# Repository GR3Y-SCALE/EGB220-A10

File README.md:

# EGB220-A10 - Line follower robot

General repository for CAD models, PCB design and firmware.

## What is the directory structure?
The initial version of this github repository has several directories that contain relevant readmes similar to this one you are reading right now, they give an example of what goes into that directory.

## Questions?
Feel free to reach out to myself or other the other project members for details and clairifcation.

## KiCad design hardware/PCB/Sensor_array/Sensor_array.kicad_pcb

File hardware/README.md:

## This directory is for everything related to CAD, such as PCB design and BOMs and 3D models and acrylic cut out files for the line following robot.

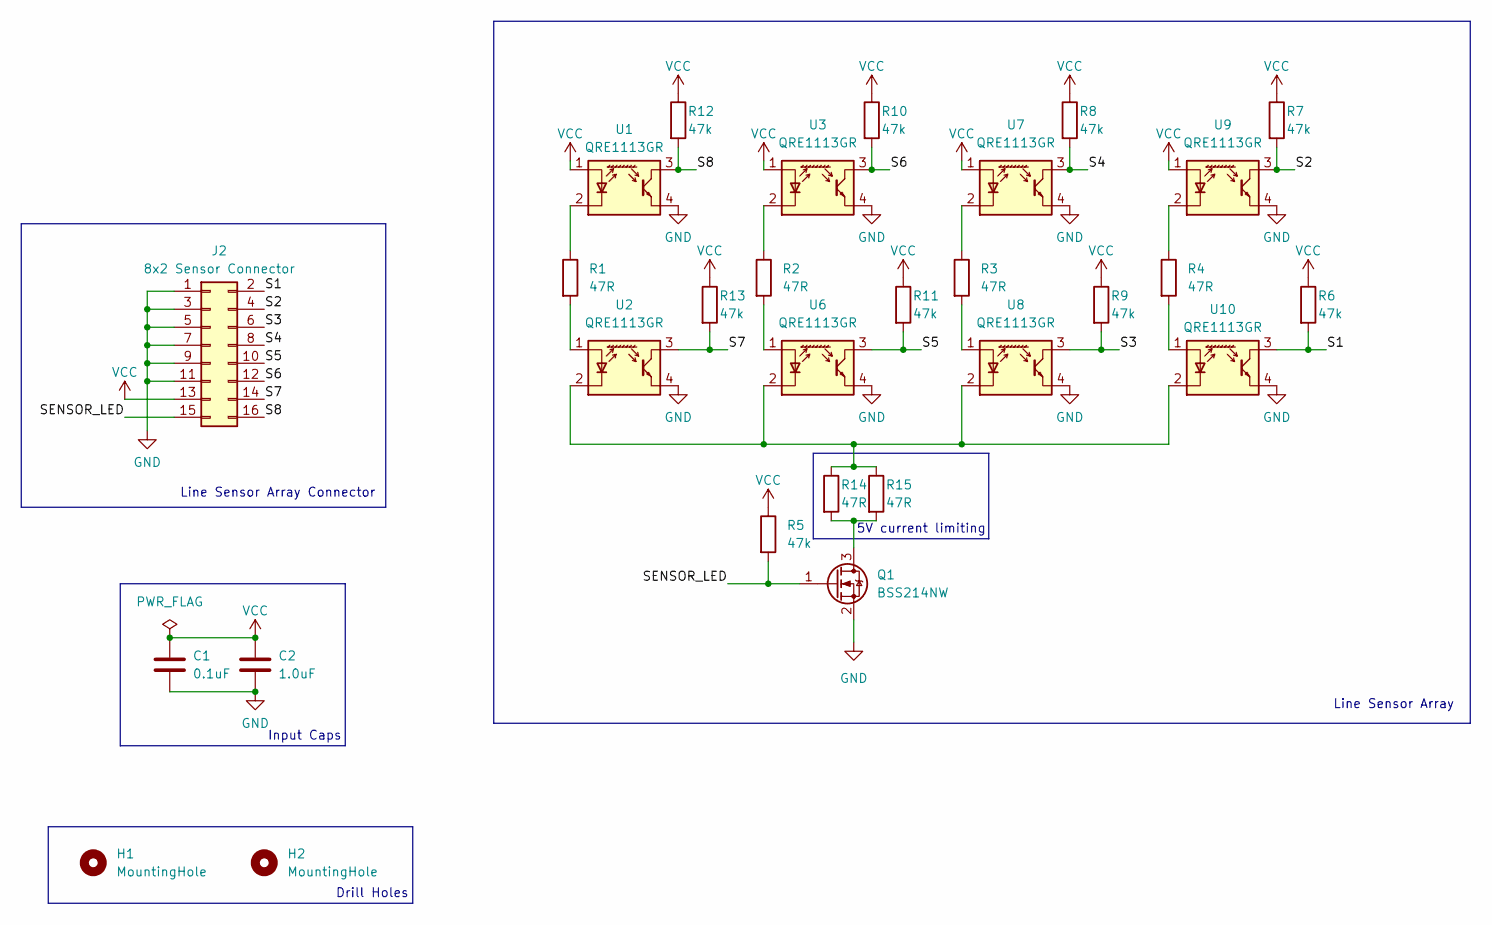
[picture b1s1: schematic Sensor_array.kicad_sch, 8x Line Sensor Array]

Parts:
C1: 0.1uF; C_0805_2012Metric; DigiKeyPartNumber 478-KGM21NR71H104KTTR-ND
C2: 1.0uF; C_0805_2012Metric; DigiKeyPartNumber 1276-1029-2-ND
H1, H2: MountingHole; MountingHole_2.2mm_M2
J2: 8x2 Sensor Connector; PinHeader_2x08_P2.54mm_Vertical
Q1: BSS214NW; SOT-323_SC-70; DigiKeyPartNumber QRE1113GRTR-ND
R1, R2, R3, R4, R14, R15: 47R; R_0805_2012Metric; DigiKeyPartNumber RMCF0805JT47R0TR-ND
R5, R6, R7, R8, R9, R10, R11, R12, R13: 47k; R_0805_2012Metric; DigiKeyPartNumber RMCF0805JT47K0TR-ND
U1, U2, U3, U6, U7, U8, U9, U10: QRE1113GR; OnSemi_CASE100CY

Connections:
/S1: J2.2, R6.2, U10.3
/S2: J2.4, R7.2, U9.3
/S3: J2.6, R9.2, U8.3
/S4: J2.8, R8.2, U7.3
/S5: J2.10, R11.2, U6.3
/S6: J2.12, R10.2, U3.3
/S7: J2.14, R13.2, U2.3
/S8: J2.16, R12.2, U1.3
/SENSOR_LED: J2.15, Q1.1 (G), R5.2
GND: C1.1, C2.1, J2.1, J2.3, J2.5, J2.7, J2.9, J2.11, Q1.2 (S), U1.4, U2.4, U3.4, U6.4, U7.4, U8.4, U9.4, U10.4
unnamed: Q1.3 (D), R14.2, R15.2
unnamed: R1.1, U1.2 (K)
unnamed: R1.2, U2.1 (A)
unnamed: R2.1, U3.2 (K)
unnamed: R2.2, U6.1 (A)
unnamed: R3.1, U7.2 (K)
unnamed: R3.2, U8.1 (A)
unnamed: R4.1, U9.2 (K)
unnamed: R4.2, U10.1 (A)
unnamed: R14.1, R15.1, U2.2 (K), U6.2 (K), U8.2 (K), U10.2 (K)
VCC: C1.2, C2.2, J2.13, R5.1, R6.1, R7.1, R8.1, R9.1, R10.1, R11.1, R12.1, R13.1, U1.1 (A), U3.1 (A), U7.1 (A), U9.1 (A)

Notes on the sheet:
Input Caps
5V current limiting
Line Sensor Array Connector
Drill Holes
Line Sensor Array

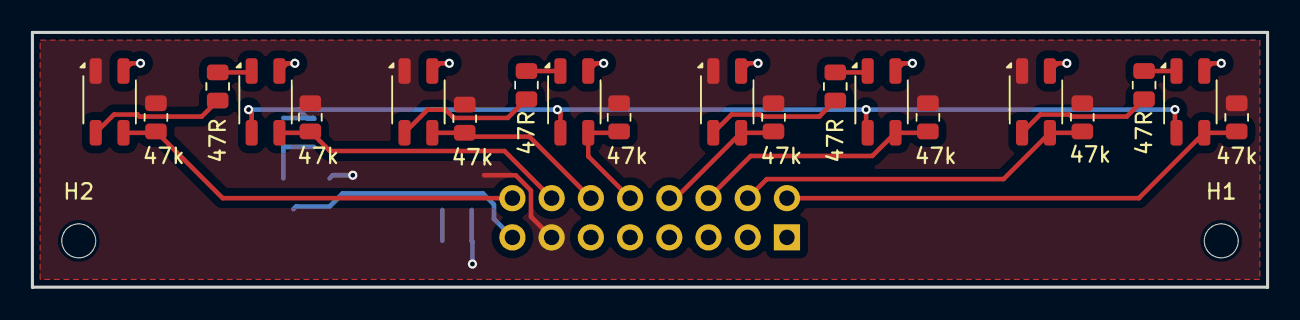
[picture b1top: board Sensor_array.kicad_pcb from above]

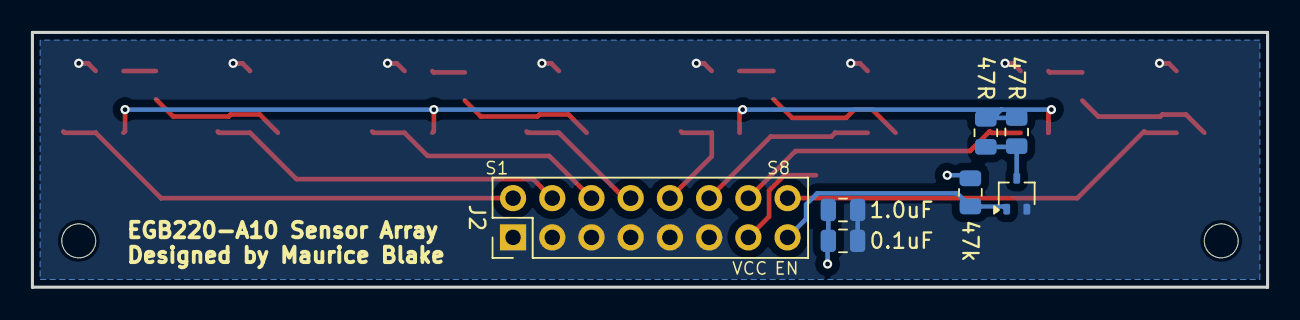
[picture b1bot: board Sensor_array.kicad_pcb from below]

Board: 2 copper layers, 80.0 x 16.5 mm, 29 parts (7 on the bottom side), 21 nets.

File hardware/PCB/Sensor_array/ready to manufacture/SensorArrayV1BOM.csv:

"Reference","Value","Datasheet","Footprint","Qty","DNP","DigiKeyPartNumber"
"C1","0.1uF","~","Capacitor_SMD:C_0805_2012Metric","1","","478-KGM21NR71H104KTTR-ND"
"C2","1.0uF","~","Capacitor_SMD:C_0805_2012Metric","1","","1276-1029-2-ND"
"J2","8x2 Sensor Connector","~","Connector_PinHeader_2.54mm:PinHeader_2x08_P2.54mm_Vertical","1","",""
"Q1","BSS214NW","https://www.infineon.com/dgdl/Infineon-BSS214NW-DS-v02_02-en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","Package_TO_SOT_SMD:SOT-323_SC-70","1","","QRE1113GRTR-ND"
"R1,R2,R3,R4,R14,R15","47R","~","Resistor_SMD:R_0805_2012Metric","6","","RMCF0805JT47R0TR-ND"
"R5,R6,R7,R8,R9,R10,R11,R12,R13","47k","~","Resistor_SMD:R_0805_2012Metric","9","","RMCF0805JT47K0TR-ND"
"U1,U2,U3,U6,U7,U8,U9,U10","QRE1113GR","http://www.onsemi.com/pub/Collateral/QRE1113-D.PDF","OptoDevice:OnSemi_CASE100CY","8","",""

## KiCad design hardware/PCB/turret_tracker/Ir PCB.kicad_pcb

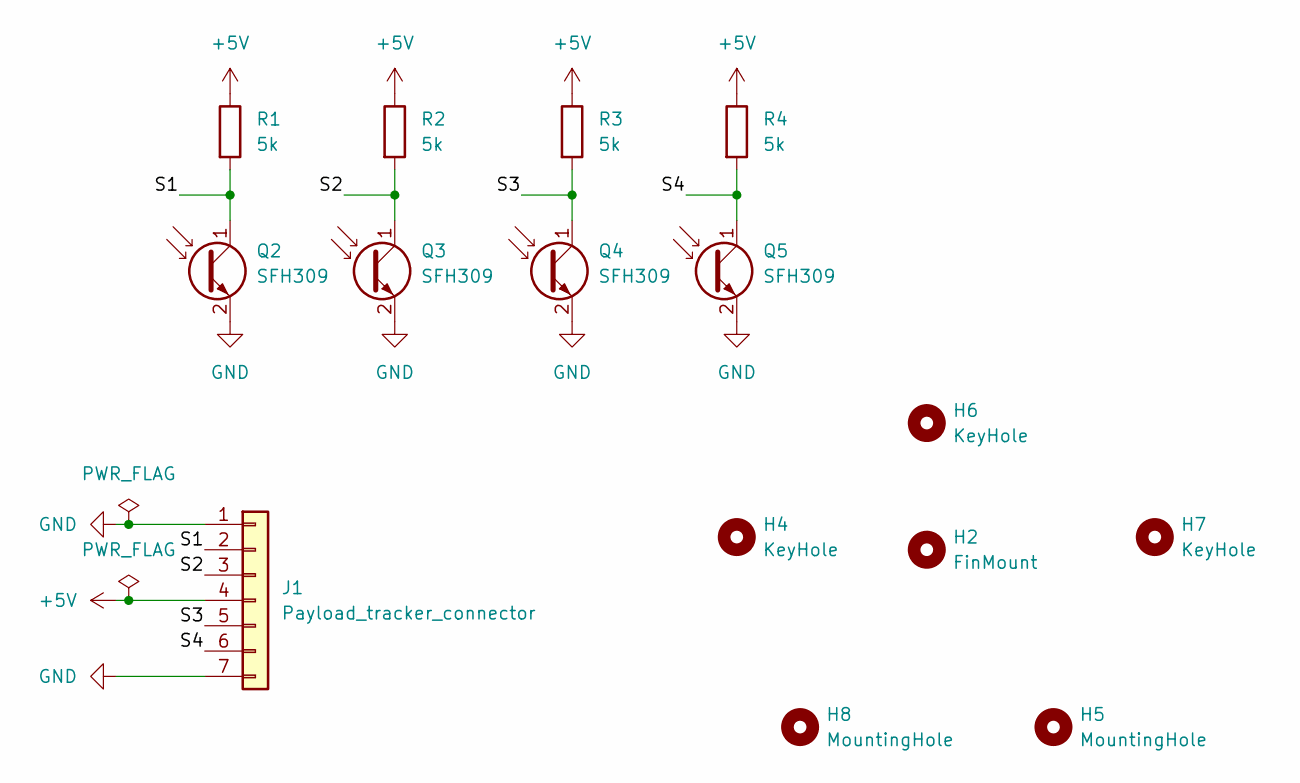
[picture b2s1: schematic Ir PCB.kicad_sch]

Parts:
H2: FinMount; MountingHole_4.3mm_M4
H4, H6, H7: KeyHole; MountingHole_2.2mm_M2
H5, H8: MountingHole; MountingHole_2.2mm_M2
J1: Payload_tracker_connector; PinHeader_1x07_P2.54mm_Vertical
Q2, Q3, Q4, Q5: SFH309; LED_D5.0mm_Clear
R1, R2, R3, R4: 5k; R_1206_3216Metric

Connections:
+5V: J1.4, R1.1, R2.1, R3.1, R4.1
/S1: J1.2, Q2.1 (C), R1.2
/S2: J1.3, Q3.1 (C), R2.2
/S3: J1.5, Q4.1 (C), R3.2
/S4: J1.6, Q5.1 (C), R4.2
GND: J1.1, J1.7, Q2.2 (E), Q3.2 (E), Q4.2 (E), Q5.2 (E)

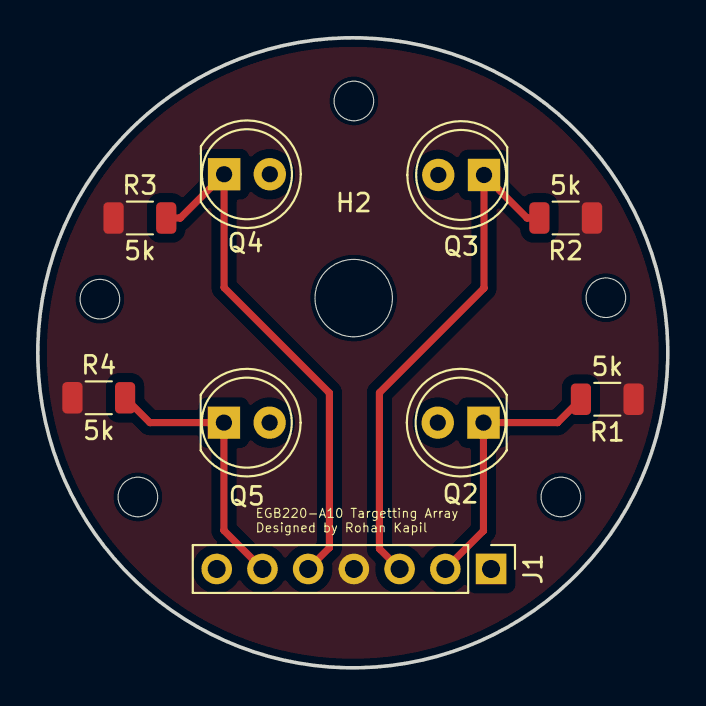
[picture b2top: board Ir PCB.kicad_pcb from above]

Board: 2 copper layers, 35.0 x 35.0 mm, 15 parts (0 on the bottom side), 6 nets.

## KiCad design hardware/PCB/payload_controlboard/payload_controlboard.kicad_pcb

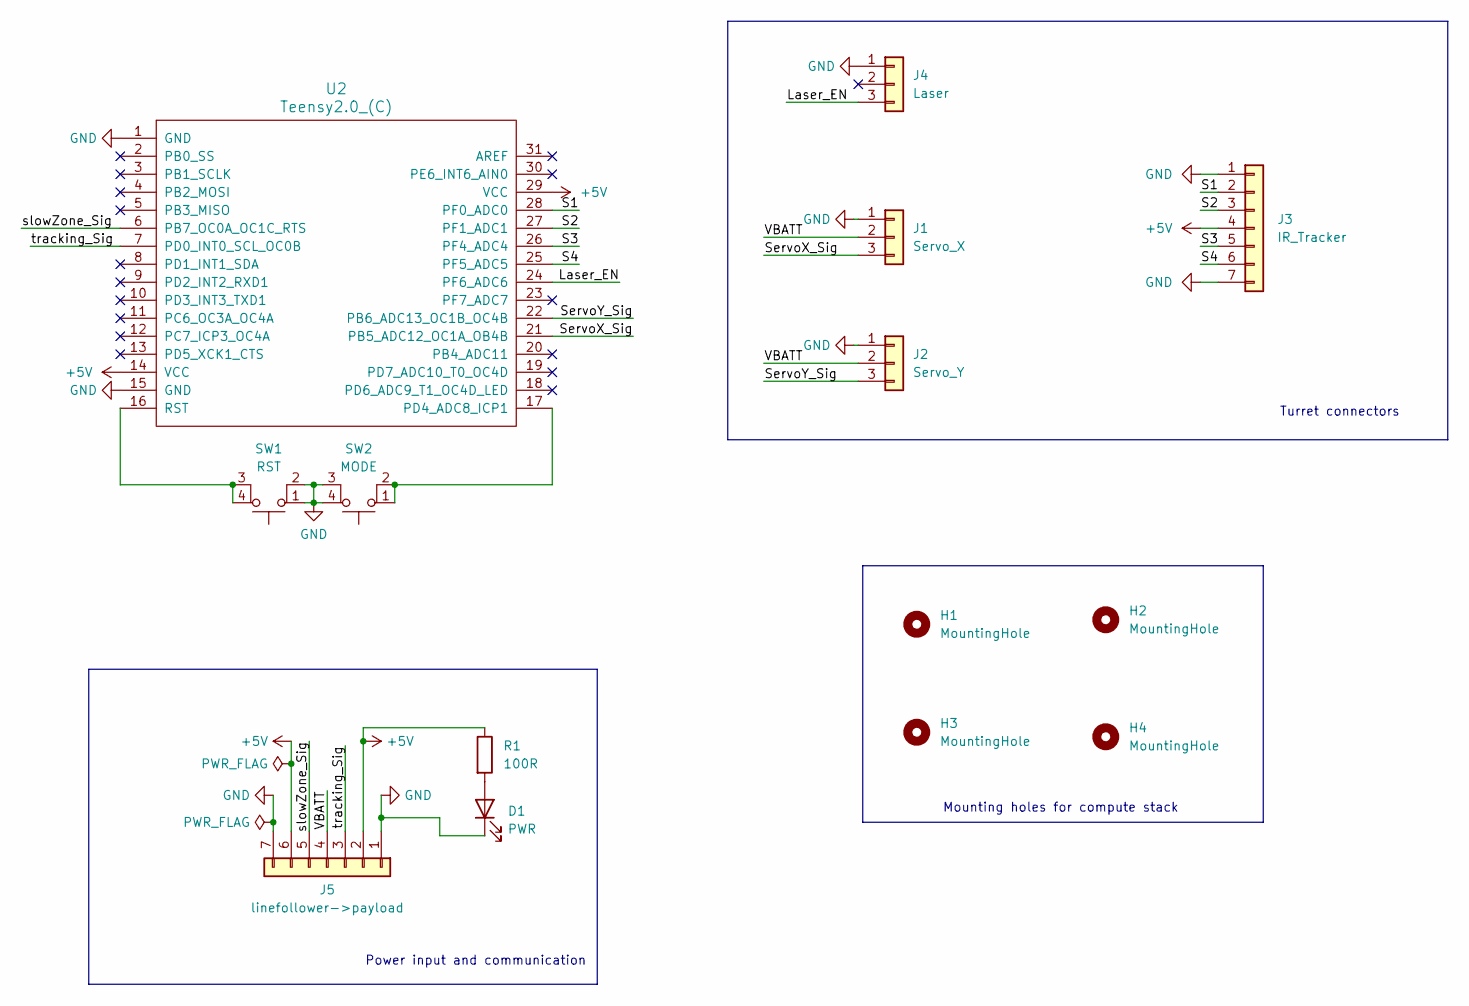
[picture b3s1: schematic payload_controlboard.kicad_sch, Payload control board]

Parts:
D1: PWR; LED_D5.0mm
H1, H2, H3, H4: MountingHole; MountingHole_3.2mm_M3
J1: Servo_X; PinHeader_1x03_P2.54mm_Vertical
J2: Servo_Y; PinHeader_1x03_P2.54mm_Vertical
J3: IR_Tracker; PinHeader_1x07_P2.54mm_Vertical
J4: Laser; PinHeader_1x03_P2.54mm_Vertical
J5: linefollower->payload; PinHeader_1x07_P2.54mm_Vertical
R1: 100R; R_Axial_DIN0207_L6.3mm_D2.5mm_P10.16mm_Horizontal
SW1: RST; SO4_222A-M-V-B_CTS
SW2: MODE; SO4_222A-M-V-B_CTS
U2: Teensy2.0_(C); Teensy2.0

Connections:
+5V: J3.4, J5.2, J5.6, R1.1, U2.14 (VCC), U2.29 (VCC)
/Laser_EN: J4.3, U2.24 (PF6_ADC6)
/S1: J3.2, U2.28 (PF0_ADC0)
/S2: J3.3, U2.27 (PF1_ADC1)
/S3: J3.5, U2.26 (PF4_ADC4)
/S4: J3.6, U2.25 (PF5_ADC5)
/ServoX_Sig: J1.3, U2.21 (PB5_ADC12_OC1A_OB4B)
/ServoY_Sig: J2.3, U2.22 (PB6_ADC13_OC1B_OC4B)
/VBATT: J1.2, J2.2, J5.4
/slowZone_Sig: J5.5, U2.6 (PB7_OC0A_OC1C_RTS)
/tracking_Sig: J5.3, U2.7 (PD0_INT0_SCL_OC0B)
GND: D1.1 (K), J1.1, J2.1, J3.1, J3.7, J4.1, J5.1, J5.7, SW1.1, SW1.2, SW2.3 (K), SW2.4 (A), U2.1 (GND), U2.15 (GND)
unnamed: D1.2 (A), R1.2
unnamed: SW1.3 (K), SW1.4 (A), U2.16 (RST)
unnamed: SW2.1, SW2.2, U2.17 (PD4_ADC8_ICP1)

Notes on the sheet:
Power input and communication
Mounting holes for compute stack
Turret connectors

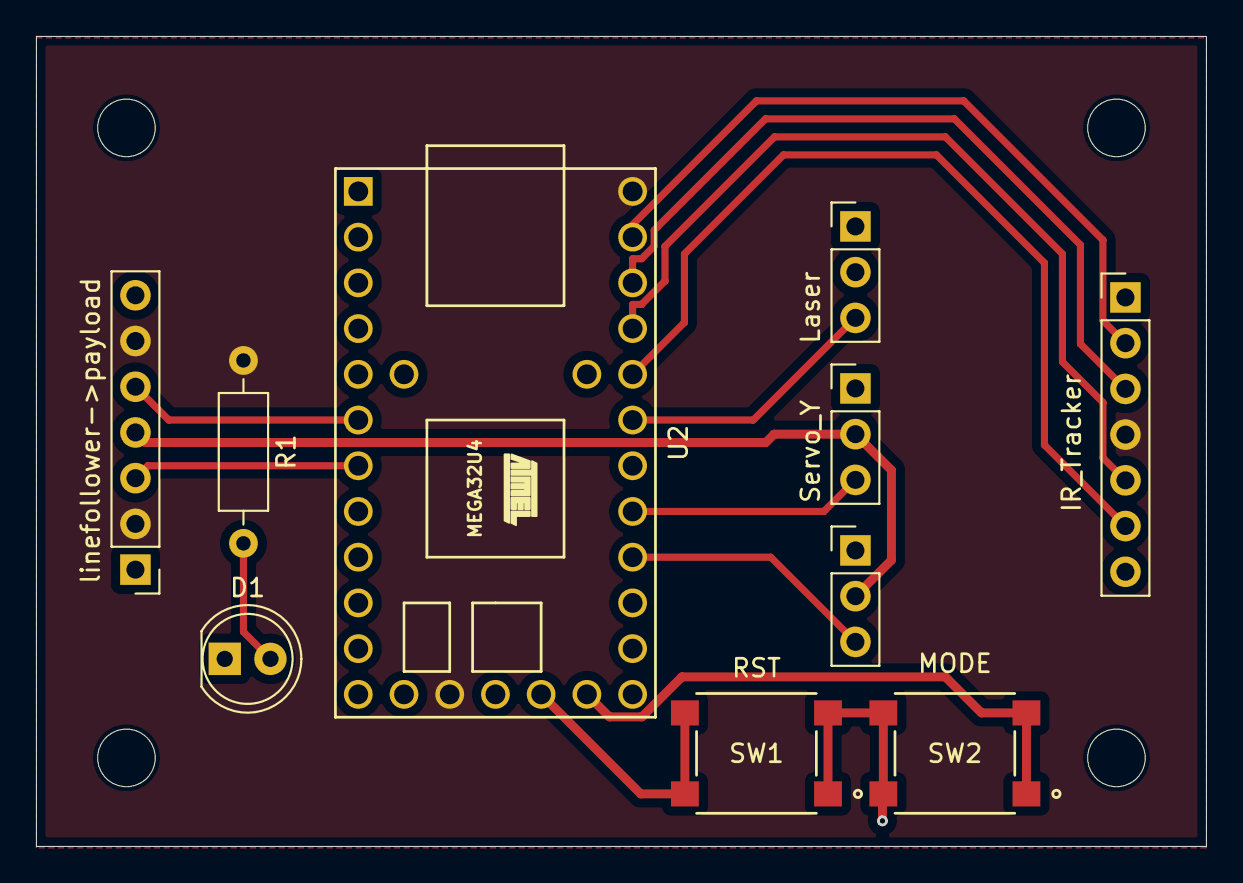
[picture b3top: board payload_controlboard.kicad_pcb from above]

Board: 2 copper layers, 65.0 x 45.0 mm, 14 parts (0 on the bottom side), 15 nets.

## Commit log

2025-02-26 Commit of directory structures and notes
2025-02-26 Added PCB dir and kicad project
2025-03-04 Added kicad schematic
2025-03-04 removed redundant directory
2025-03-06 Added minimal viable product stage 1 reference CAD files
2025-03-19 Chassis PCB schematic initial layout
2025-03-20 initial sofware layout with pio
2025-03-20 added init code
2025-03-24 Created prototype sensor array schematic and PCB, revised mainboard
2025-03-24 Flipped connector and added insightful silkscreen to sensor array
2025-03-24 added teensy 2.0 symbol for payload subsystem
2025-03-24 added init schematic
2025-03-29 Initial payload control board and connector layout
2025-03-30 Added payload connectors and follower->payload compliant connector
2025-04-01 Switched line follower code to PlatformIO
2025-04-01 testing branches
2025-04-01 Finished PCBs for payload and turret
2025-04-03 Added gitignore to ignore cache files for mac and kicad
2025-04-03 Added payload pio config and layout
2025-04-03 Added main.cpp function structure prior to writing code
2025-04-03 Initial tracking code with calibration, no hysteresis atm
2025-04-03 fixed IR Sensor order, 3,2,4,1 instead of 1,2,3,4
2025-04-05 reversed sensor order, 8->1 instead 1->8
2025-04-05 Added arduino uno compatible code for testing with Jack
2025-04-05 added serial debug
2025-04-05 Partially working
2025-04-05 code cleanup
2025-04-05 Fixed logic of sensor detection
2025-04-05 Final rev before test
2025-04-05 Removed floating point arithmetic
2025-04-07 tweaked PID values and threshold, now running code
2025-04-08 Tweaks to code
2025-04-08 kicad backup
2025-04-09 MVP demp ready code, CAD and documents
2025-04-09 MVP ready
2025-04-09 moved CAD files to correct directory
2025-04-15 Learning github
2025-05-01 Payload controller
2025-05-01 Remove and ignore .DS_Store
2025-05-01 payload v2
2025-05-01 finalised mainboard design
2025-05-08 state machine for line follower
2025-05-08 minor changes
2025-05-14 Jack's Attempt at LED code
2025-05-14 with led code
2025-05-14 Alternating Path
2025-05-31 Code clean up, debug state added, state machine for payload added
2025-06-06 Working final demo code and fixes
2025-06-07 Final project commit
